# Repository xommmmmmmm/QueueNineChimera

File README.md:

# Q9 Chimera & Limousine

Q9 Chimera & Limousine are RP2040-based, drop-in, multi-layout replacement PCBs for Keychron Q9. Chimera supports ortholinear layout with central or right-hand numpad, and traditional row-stagger with right hand numpad. Limousine supports row and alpha stagger, with support for 2.25u/2.75u "Alice" bars and right-hand numpad.

Both versions support up to two independent EC11 rotary encoders in the separated key positions, and a plethora of bottom-row options.

*xomm's split ortho build*

*baconspoon's row-staggered build*

## Hardware

* Keyboard Maintainer: [xomm](https://github.com/xommmmmmmm) and [baconspoon](https://github.com/baconspoon85)
* Hardware Supported: Keychron Q9, Keychron Q9 Plus cases with Q9 Chimera PCB
* Hardware Availability: Case from [Keychron](https://www.keychron.com/products/keychron-q9-qmk-custom-mechanical-keyboard), Open-source PCB orderable from JLCPCB using provided production files in their respective subfolders. Production files should be orderable as-is and have been used successfully for PCBA, but no guarantees or warranties are made. 

This project is not affiliated with or endorsed by Keychron or JLCPCB.

### Build Guide

**Disassembly**:
1. If you have keycaps on the board, remove them before disassembly to avoid scratching them against the case.
1. Flip the board upside down and unscrew the six H2.5 screws on the bottom case to remove it.
1. Disconnect the JST connector from the original board
1. Lift the assembly out by lifting from the bottom (spacebar side) first, then pull it out from under the daughterboard. Take care not to lose the 3 plastic caps from the pegs on the top case.

**Test the new PCB**:
1. Insert 2 switches in the top left for unlocking the board.
1. Connect the JST from the daughterboard to the new board.
1. Taking care to not short any board components on the top case, connect the USB-C to your PC.
1. Open https://vial.rocks/ to validate that it is detected.
1. Open the matrix tester and use tweezers or a switch puller to check sockets.
1. Disconnect USB-C once done, then disconnect the JST.

**PCB Assembly**:
1. If you have a barebones PCB and/or want to add EC11 encoder(s), now is the time to solder. 
    1. If you are not using encoder(s), and you originally purchased the Q9 with one, remove the PH1 screws holding in the encoder blocker from the top case. 
1. Add any PCB-mounted stabilizers you will be using. If your switches have minimal wobble, you generally won't need 2u stabilizers.  
    1. Limousine note: If you chose to have Mill-Max sockets soldered for 3u spacebars, you will need to desolder one of the Kailh hotswap sockets to access a 3u stabilizer hole. Conversely, the 3u Mill-Max sockets sit under the stabilizers of other footprints, so you may want to add pads under your stabilizers to reduce the bottom-out noise.

**Plate Assembly**:
1. When inserting switches, support the hotswap socket from the back to avoid accidental damage in case of misalignment. Reference the KLE for your desired layout if unsure which footprints to use.
1. To align the plate, place switches around the border of the plate and a few in the top row, then assemble the plate to the PCB.
1. To minimize plate flex when inserting switches, fill out the remaining switches from right to left, top to bottom.
1. If you will be reusing the original foam gaskets, remove them carefully by picking at one side until all the adhesive is lifted, then slowly peel it off the plate.
1. If you will be using the included gaskets from the kit, they are unfortunately short, but will function and sound pretty much the same.
    1. You can choose to use them as-is and stick them in the middle, or cut them in half and stick them on the edges.
1. Apply the gaskets on both sides of the plate (eight total), using tweezers is recommended.

**Case Assembly**:
1. Insert the assembly into the top case, putting the top under the daughterboard first, then aligning the mounting holes on the plate with the pegs in the top case. Pay attention to the six screw posts since they might catch on their cutouts in plate a bit. There might be a little bit of friction at first but it will seat once everything is aligned, heavy force is not required. 
1. Tape modding the bottom of the PCB or the inside of the bottom case, either with the stock cardboard adhesive and/or 3M painter's tape is highly recommended. This will prevent unlikely but possible shorts from bottoming out the PCB on aftermarket gaskets if you press hard.
1. Close the bottom case, add keycaps, set up your layout in Vial.
    1. In Vial, use the Layouts tab to select the physical layout options you want. For the 8u/10u spacebar option on Chimera v1.1, select the first 6u bar option and simply leave the unused keys blank.
3. Enjoy! (And maybe send a pic of your completed build in the mini-GB channel on the 40% Keyboards Discord server!)

## Firmware

PCBs purchases from the mini-GB are pre-flashed. Vial firmware source can be found [here](https://github.com/xommmmmmmm/vial-qmk/tree/q9_chimera_v1.1/keyboards/q9_dropin). Pre-compiled firmware can be found [here](https://github.com/xommmmmmmm/QueueNineChimera/tree/main/firmware/). 

# Q9 Chimera keymap options

All sockets for all layout options can be populated during PCB assembly, including the ones under the encoders.

- [Chimera v1.0 Keyboard Layout Editor gist](https://www.keyboard-layout-editor.com/#/gists/b5c5bf3bcd11c2a14bd86eb9c05d4cf7)
- [Chimera v1.1 Keyboard Layout Editor gist](https://www.keyboard-layout-editor.com/#/gists/ead72f9d526c6d2558d7e2d7f39707f8)

- [Limousine v1.0 Keyboard Layout Editor gist](https://www.keyboard-layout-editor.com/#/gists/2bb4640f105051db48f84b30d6797b1b)

## Options

The images at the top use the following options:
- xomm's split ortho layout:
  - Spacebar option 8: 1-2-1-1-1
  - Split Ortho, Right 2u Spacebar
- baconspoon's row-staggered layout:
  - Row Stagger
  - Spacebar option 2: 6 (off-center, flipped)
  - Right Numpad, 2u Zero

The default keymap is provided as barebones due to the number of possible layouts, and should be edited as desired. Remember to export your .vil from Vial GUI once satisfied for safekeeping.

## Credits and helpful things

- Big thanks to baconspoon for validating the design, contributing plate/edge cuts, additional layouts, and a ton of other help.
- Noah Kiser's [TKL RP2040 PCB Design](https://www.youtube.com/watch?v=6Z49bynRqj8&list=PLstjCi968EZftHZSitvqiVnyZ1CbmptIB) series
- Joe Scotto's [PCB Design](https://www.youtube.com/watch?v=7LyziNdFlew&list=PLBD2IS_t_iWZDMdG_ZF57x9Ebm3kxKqxF) series

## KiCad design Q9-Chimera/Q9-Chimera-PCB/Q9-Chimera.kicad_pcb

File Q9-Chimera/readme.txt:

Q9 Chimera is a Drop-in multi-layout PCB for Keychron Q9.
Supports ortholinear layout with central or right-hand numpad, and traditional row-stagger with right hand numpad.
Supports up to two independent rotory encoder positions. 
6u spacebar option supports off-center switch position in either the standard orientation or flipped.

http://www.keyboard-layout-editor.com/#/gists/67177e22bc722249cd7f5064d6e78f69

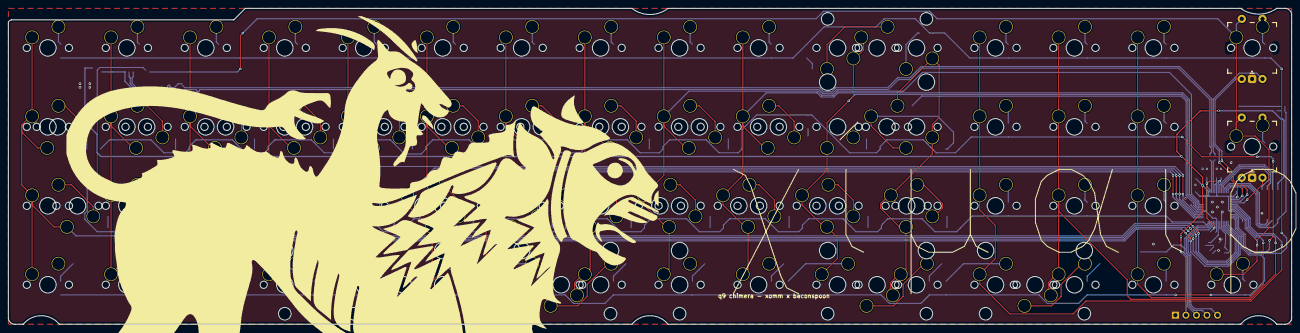
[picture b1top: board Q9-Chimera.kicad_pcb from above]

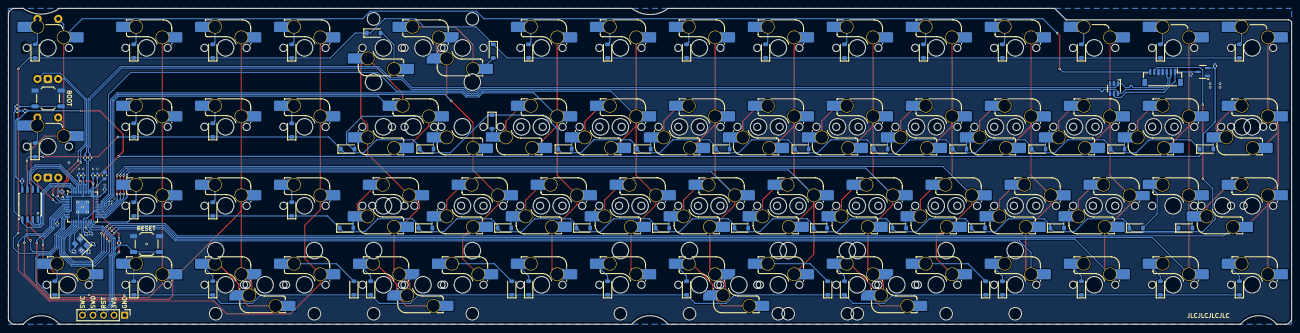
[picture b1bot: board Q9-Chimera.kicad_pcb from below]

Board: 2 copper layers, 309.6 x 76.2 mm, 194 parts (185 on the bottom side), 109 nets.

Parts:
BOOT1: SW_Push; SW_SPST_TL3342
C1, C2, C3, C6, C11: 1u; C_0402_1005Metric
C4, C7, C8, C9, C13, C14, C15, C16: 100n; C_0402_1005Metric
C5: 10u; C_0603_1608Metric
C10, C12: 22p; C_0402_1005Metric
D1, D2, D3, D4, D5, D6, D7, D8, D9, D10, D11, D12, D13, D14, D15, D16, D17, D18, D19, D20, D21, D22, D23, D24, D25, D26, D27, D28, D29, D30, D31, D32, D33, D34, D35, D36, D37, D38, D39, D40, D41, D42, D43, D44, D45, D46, D47, D48, D49, D50, D51, D52, D54, D55, D56, D57, D58, D59, D61, D62, D63, D64, D65: D_Small; D_SOD-123_xomm
J1: Conn_01x07; JST_SH_BM07B-SRSS-TB_1x07-1MP_P1.00mm_Vertical
J3: Conn_01x05; PinHeader_1x05_P2.54mm_Vertical
MX1, MX2, MX3, MX16, MX32: MX_SW_HS; SW_MX_HS_S_CPG151101S11_1u
MX4, MX5, MX6, MX7, MX8, MX9, MX10, MX11, MX12, MX13, MX14, MX15, MX17, MX18, MX19, MX20, MX21, MX22, MX23, MX24, MX25, MX26, MX27, MX28, MX29, MX30, MX31, MX33, MX34, MX35, MX36, MX37, MX38, MX39, MX40, MX41, MX42, MX43, MX44, MX45, MX46, MX47, MX48, MX49, MX50, MX51, MX52, MX53, MX54, MX55, MX56, MX57, MX58, MX59, MX60, MX61, MX62, MX63, MX64, MX65, MX66, MX67, MX68, MX70, MX71, MX72, MX73, MX74, MX75, MX76, MX77, MX78, MX81, MX82, MX83, MX84, MX85, MX86, MX87, MX88, MX89: MX_SW_HS; SW_MX_HS_CPG151101S11_1u
MX69, MX90: MX_SW_HS; SW_MX_HS_CPG151101S11_1.25u
MX79, MX80: MX_SW_HS; SW_MX_HS_CPG151101S11_1.75u
R3, R4, R5: 5.1k; R_0402_1005Metric
R6, R9: 1k; R_0402_1005Metric
R7, R8: 27; R_0402_1005Metric
RST1: SW_Push; SW_SPST_TL3342
S1, S2, S3, S4, S7: MX_stab; STAB_MX_2u
S5, S6: MX_stab; STAB_MX_3u
SW1, SW2: RotaryEncoder_Switch; ROT_Alps_EC11E-Switch
U1: XC6206PxxxMR; SOT-23-3
U2: SRV05-4; SOT-23-6-routable
U3: RP2040; QFN-56-1EP_7x7mm_P0.4mm_EP3.2x3.2mm
U4: W25Q128JVS; SOIC-8_5.23x5.23mm_P1.27mm
Y1: Crystal_GND24; Crystal_SMD_3225-4Pin_3.2x2.5mm

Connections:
+1V1: C3.1, C4.1, C16.1, U3.23 (DVDD), U3.45 (VREG_VOUT), U3.50 (DVDD)
+3V3: C2.1, C5.1, C6.1, C7.1, C8.1, C9.1, C11.1, C13.1, C14.1, C15.1, J3.2, R3.1, R5.1, U1.2 (VO), U3.1 (IOVDD), U3.10 (IOVDD), U3.22 (IOVDD), U3.33 (IOVDD), U3.42 (IOVDD), U3.43 (ADC_AVDD), U3.44 (VREG_IN), U3.48 (USB_VDD), U3.49 (IOVDD), U4.8 (VCC)
+5V: C1.1, J1.1, U1.3 (VI), U2.5 (VP)
Col 0: MX1.1, MX17.1, MX33.1, MX48.1, MX69.1, MX80.1, U3.18 (GPIO15)
Col 1: MX2.1, MX18.1, MX34.1, MX49.1, MX70.1, U3.17 (GPIO14)
Col 2: MX3.1, MX19.1, MX35.1, MX50.1, MX71.1, MX81.1, U3.16 (GPIO13)
Col 3: MX4.1, MX20.1, MX36.1, MX51.1, MX72.1, MX82.1, U3.15 (GPIO12)
Col 4: MX5.1, MX21.1, MX37.1, MX52.1, MX73.1, MX83.1, U3.32 (GPIO21)
Col 5: MX6.1, MX22.1, MX38.1, MX53.1, MX54.1, MX74.1, MX84.1, U3.31 (GPIO20)
Col 6: MX7.1, MX23.1, MX39.1, MX55.1, MX75.1, MX85.1, U3.30 (GPIO19)
Col 7: MX8.1, MX24.1, MX40.1, MX56.1, MX66.1, MX76.1, MX86.1, U3.29 (GPIO18)
Col 8: MX9.1, MX25.1, MX41.1, MX57.1, MX77.1, MX87.1, U3.37 (GPIO25)
Col 9: MX10.1, MX26.1, MX42.1, MX58.1, MX78.1, MX88.1, U3.36 (GPIO24)
Col 10: MX11.1, MX27.1, MX43.1, MX59.1, MX68.1, MX89.1, U3.35 (GPIO23)
Col 11: MX12.1, MX28.1, MX44.1, MX60.1, MX61.1, MX79.1, MX90.1, U3.34 (GPIO22)
Col 12: MX13.1, MX29.1, MX45.1, MX62.1, U3.6 (GPIO4)
Col 13: MX14.1, MX30.1, MX46.1, MX63.1, MX67.1, U3.7 (GPIO5)
Col 14: MX15.1, MX31.1, MX47.1, MX64.1, U3.8 (GPIO6)
Col 15: J1.7, MX16.1, MX32.1, MX65.1, SW1.S2, SW2.S2, U3.9 (GPIO7)
D+: J1.3, R7.1, U2.1 (IO1)
D-: J1.2, R8.1, U2.6 (IO4)
ENC1A: SW1.A, U3.3 (GPIO1)
ENC1B: SW1.B, U3.2 (GPIO0)
ENC2A: SW2.A, U3.4 (GPIO2)
ENC2B: SW2.B, U3.5 (GPIO3)
GND: BOOT1.1, C1.2, C2.2, C3.2, C4.2, C5.2, C6.2, C7.2, C8.2, C9.2, C10.1, C11.2, C12.1, C13.2, C14.2, C15.2, C16.2, J1.4, J1.5, J3.1, RST1.1, SW1.C, SW2.C, U1.1 (GND), U2.2 (VN), U3.19 (TESTEN), U3.57 (GND), U4.4 (GND), Y1.2, Y1.4
unnamed: BOOT1.2, R6.1
unnamed: C12.2, R9.1, Y1.1
unnamed: D1.2 (A), MX1.2
unnamed: D2.2 (A), MX2.2
unnamed: D3.2 (A), MX3.2
unnamed: D4.2 (A), MX4.2
unnamed: D5.2 (A), MX5.2
unnamed: D6.2 (A), MX6.2
unnamed: D7.2 (A), MX7.2
unnamed: D8.2 (A), MX8.2
unnamed: D9.2 (A), MX9.2
unnamed: D10.2 (A), MX10.2
unnamed: D11.2 (A), MX11.2, MX68.2
unnamed: D12.2 (A), MX12.2
unnamed: D13.2 (A), MX13.2
unnamed: D14.2 (A), MX14.2
unnamed: D15.2 (A), MX15.2
unnamed: D16.2 (A), MX16.2, SW1.S1
unnamed: D17.2 (A), MX17.2, MX69.2
unnamed: D18.2 (A), MX18.2, MX70.2
unnamed: D19.2 (A), MX19.2, MX71.2
unnamed: D20.2 (A), MX20.2, MX72.2
unnamed: D21.2 (A), MX21.2, MX73.2
unnamed: D22.2 (A), MX22.2, MX74.2
unnamed: D23.2 (A), MX23.2, MX75.2
unnamed: D24.2 (A), MX24.2, MX76.2
unnamed: D25.2 (A), MX25.2, MX77.2
unnamed: D26.2 (A), MX26.2, MX78.2
unnamed: D27.2 (A), MX27.2
unnamed: D28.2 (A), MX28.2, MX79.2
unnamed: D29.2 (A), MX29.2
unnamed: D30.2 (A), MX30.2
unnamed: D31.2 (A), MX31.2
unnamed: D32.2 (A), MX32.2, SW2.S1
unnamed: D33.2 (A), MX33.2, MX80.2
unnamed: D34.2 (A), MX34.2
unnamed: D35.2 (A), MX35.2, MX81.2
unnamed: D36.2 (A), MX36.2, MX82.2
unnamed: D37.2 (A), MX37.2, MX83.2
unnamed: D38.2 (A), MX38.2, MX84.2
unnamed: D39.2 (A), MX39.2, MX85.2
unnamed: D40.2 (A), MX40.2, MX86.2
unnamed: D41.2 (A), MX41.2, MX87.2
unnamed: D42.2 (A), MX42.2, MX88.2
unnamed: D43.2 (A), MX43.2, MX89.2
unnamed: D44.2 (A), MX44.2, MX90.2
unnamed: D45.2 (A), MX45.2
unnamed: D46.2 (A), MX46.2
unnamed: D47.2 (A), MX47.2
unnamed: D48.2 (A), MX48.2
unnamed: D49.2 (A), MX49.2
unnamed: D50.2 (A), MX50.2
unnamed: D51.2 (A), MX51.2
unnamed: D52.2 (A), MX52.2
unnamed: D54.2 (A), MX53.2, MX54.2
unnamed: D55.2 (A), MX55.2
unnamed: D56.2 (A), MX56.2, MX66.2
unnamed: D57.2 (A), MX57.2
unnamed: D58.2 (A), MX58.2
unnamed: D59.2 (A), MX59.2
unnamed: D61.2 (A), MX60.2, MX61.2
unnamed: D62.2 (A), MX62.2
unnamed: D63.2 (A), MX63.2, MX67.2
unnamed: D64.2 (A), MX64.2
unnamed: D65.2 (A), MX65.2
unnamed: R3.2, R4.1
unnamed: R8.2, U3.46 (USB_DM)
unnamed: R7.2, U3.47 (USB_DP)
Q_CLK: U3.52 (QSPI_SCLK), U4.6 (CLK)
Q_IO0: U3.53 (QSPI_SD0), U4.5 (DI(IO0))
Q_IO1: U3.55 (QSPI_SD1), U4.2 (DO(IO1))
Q_IO2: U3.54 (QSPI_SD2), U4.3 (IO2)
Q_IO3: U3.51 (QSPI_SD3), U4.7 (IO3)
Q_SEL: R4.2, R6.2, U3.56 (QSPI_SS), U4.1 (~CS)
RESET: J3.3, R5.2, RST1.2, U3.26 (RUN)
Row 0: D1.1 (K), D2.1 (K), D3.1 (K), D4.1 (K), D5.1 (K), D6.1 (K), D7.1 (K), D8.1 (K), D9.1 (K), D10.1 (K), D11.1 (K), D12.1 (K), D13.1 (K), D14.1 (K), D15.1 (K), D16.1 (K), U3.13 (GPIO10)
Row 1: D17.1 (K), D18.1 (K), D19.1 (K), D20.1 (K), D21.1 (K), D22.1 (K), D23.1 (K), D24.1 (K), D25.1 (K), D26.1 (K), D27.1 (K), D28.1 (K), D29.1 (K), D30.1 (K), D31.1 (K), D32.1 (K), U3.12 (GPIO9)
Row 2: D33.1 (K), D34.1 (K), D35.1 (K), D36.1 (K), D37.1 (K), D38.1 (K), D39.1 (K), D40.1 (K), D41.1 (K), D42.1 (K), D43.1 (K), D44.1 (K), D45.1 (K), D46.1 (K), D47.1 (K), J1.6, U3.27 (GPIO16)
Row 3: D48.1 (K), D49.1 (K), D50.1 (K), D51.1 (K), D52.1 (K), D54.1 (K), D55.1 (K), D56.1 (K), D57.1 (K), D58.1 (K), D59.1 (K), D61.1 (K), D62.1 (K), D63.1 (K), D64.1 (K), D65.1 (K), U3.14 (GPIO11)
SWC: J3.5, U3.24 (SWCLK)
SWD: J3.4, U3.25 (SWD)
XIN: C10.2, U3.20 (XIN), Y1.3
XOUT: R9.2, U3.21 (XOUT)

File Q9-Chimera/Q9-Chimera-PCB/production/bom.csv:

Designator,Footprint,Quantity,Value,LCSC Part #
"BOOT1, RST1",SW_SPST_TL3342,2,SW_Push,
"C1, C11, C2, C3, C6",0402,5,1u,
"C10, C12",0402,2,22p,
"C13, C14, C15, C16, C4, C7, C8, C9",0402,8,100n,
C5,0603,1,10u,
"D1, D10, D11, D12, D13, D14, D15, D16, D17, D18, D19, D2, D20, D21, D22, D23, D24, D25, D26, D27, D28, D29, D3, D30, D31, D32, D33, D34, D35, D36, D37, D38, D39, D4, D40, D41, D42, D43, D44, D45, D46, D47, D48, D49, D5, D50, D51, D52, D54, D55, D56, D57, D58, D59, D6, D61, D62, D63, D64, D65, D7, D8, D9",D_SOD-123_xomm,63,D_Small,
J1,JST_SH_BM07B-SRSS-TB_1x07-1MP_P1.00mm_Vertical,1,Conn_01x07,
"MX1, MX16, MX2, MX3, MX32",SW_MX_HS_S_CPG151101S11_1u,5,MX_SW_HS,
"MX10, MX11, MX12, MX13, MX14, MX15, MX17, MX18, MX19, MX20, MX21, MX22, MX23, MX24, MX25, MX26, MX27, MX28, MX29, MX30, MX31, MX33, MX34, MX35, MX36, MX37, MX38, MX39, MX4, MX40, MX41, MX42, MX43, MX44, MX45, MX46, MX47, MX48, MX49, MX5, MX50, MX51, MX52, MX53, MX54, MX55, MX56, MX57, MX58, MX59, MX6, MX60, MX61, MX62, MX63, MX64, MX65, MX66, MX67, MX68, MX7, MX70, MX71, MX72, MX73, MX74, MX75, MX76, MX77, MX78, MX8, MX81, MX82, MX83, MX84, MX85, MX86, MX87, MX88, MX89, MX9, MX91, MX92, MX95",SW_MX_HS_CPG151101S11_1u,84,MX_SW_HS,
"MX69, MX90",SW_MX_HS_CPG151101S11_1.25u,2,MX_SW_HS,
"MX79, MX80",SW_MX_HS_CPG151101S11_1.75u,2,MX_SW_HS,
"R3, R4, R5",0402,3,5.1k,
"R6, R9",0402,2,1k,
"R7, R8",0402,2,27,
"S1, S2, S3, S4, S7, S8, S9",STAB_MX_2u,7,MX_stab_2u,
"S10, S5, S6",STAB_MX_3u,3,MX_stab_3u,
S13,STAB_MX_10u,1,MX_stab_7810u,
U1,SOT-23-3,1,XC6206PxxxMR,
U2,SOT-23-6-routable,1,SRV05-4,
U3,QFN-56-1EP_7x7mm_P0.4mm_EP3.2x3.2mm,1,RP2040,
U4,SOIC-8_5.23x5.23mm_P1.27mm,1,W25Q128JVS,
Y1,Crystal_SMD_3225-4Pin_3.2x2.5mm,1,Crystal_GND24,

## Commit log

2024-05-30 add encoders, ground fill, production files
2024-05-30 trach connect
2024-05-30 remove plating from encoder mounts
2024-05-30 fix silkscreen/solder mask conflicts
2024-05-30 update production files
2024-05-30 add back right side numpad layout
2024-05-30 fix spacebar routing
2024-05-30 route vias away from top case resting point
2024-06-01 add spacebar for 3u center cluster
2024-06-01 add ortho plate subproject
2024-06-03 initial commit for q9-chimera multi-layout dropin
2024-06-03 commit chimera and associated plate directory
2024-06-04 unzip gerbers
2024-06-07 added missing solder mask apertures and updated gerbers to reflect change
2024-06-26 reorganizing repo
2024-06-26 update gerbers and kle
2024-06-27 release prep
2024-06-27 add credits
2024-06-28 add baconspoon image and layout option examples
2024-08-10 add 2 additional 2u footprints
2024-08-24 complete addition of 225/275 bars and associated tweaks
2024-08-25 testing more THT
2024-09-11 add new spacebar pcb stab cutouts to plate, except long bars
2024-09-15 split 225/275 to limousine, add 8u/10u support
2024-09-18 prep production files
2024-09-18 swap conflicting sockets for solder/millmax
2024-10-16 Update README.md with build guide
2024-10-21 prep v1.1 release
2024-10-22 update links and readme
